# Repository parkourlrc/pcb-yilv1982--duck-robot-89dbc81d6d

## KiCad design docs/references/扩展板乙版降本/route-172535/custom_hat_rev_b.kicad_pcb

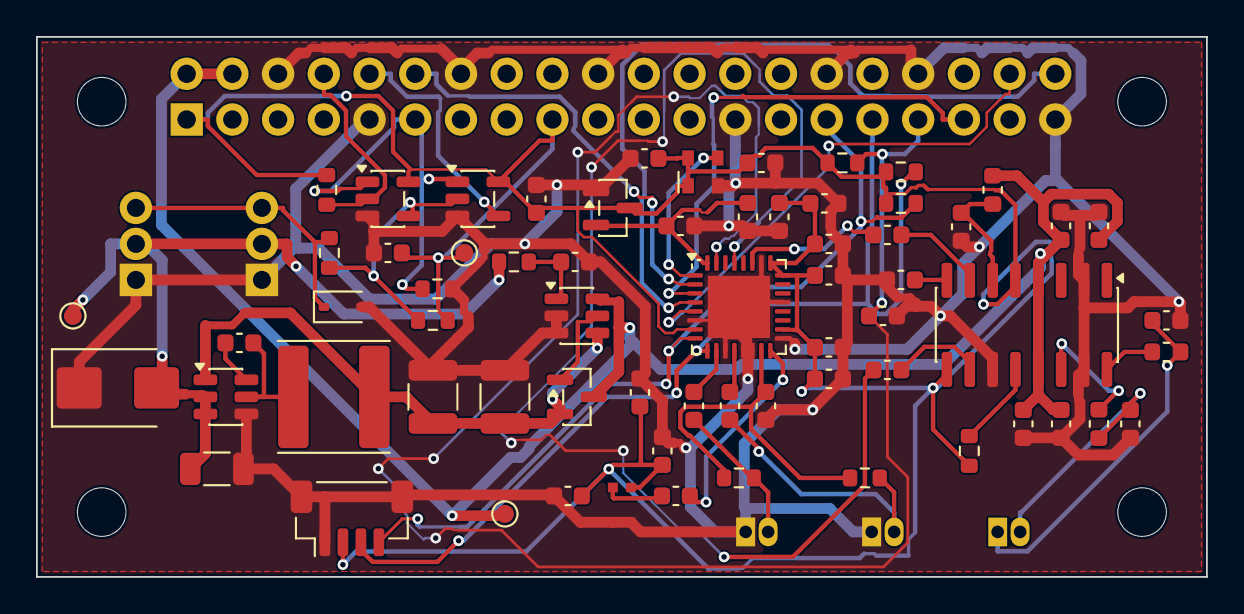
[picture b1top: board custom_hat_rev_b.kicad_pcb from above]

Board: 2 copper layers, 65.0 x 30.0 mm, 76 parts (1 on the bottom side), 41 nets.

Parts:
C301: 10uF35V; C_1206_3216Metric
C302, C305, C401, C402, C701, C704, C705, C707, C709, C711, C713, C721, C725, C735, C737: 100nF; C_0603_1608Metric
C303, C304: 22uF25V; C_1210_3225Metric
C702, C706, C708, C710, C712, C722, C723, C724, C731, C732, C733, C738: 1uF; C_0603_1608Metric
C703, C734, C736: 10uF; C_0603_1608Metric
C739, C740: 220pF; C_0603_1608Metric
D301: SMBJ12A; D_SMB
D401: 5.1V; D_SOD-323
FB701: 600R@100MHz; L_0603_1608Metric
FB702, FB703: 120R@100MHz; L_0603_1608Metric
H1, H2: MountingHole_2.7mm_M2.5; MountingHole_2.7_M2.5_Head4.5
H3, H4: MountingHole_2.7mm_M2.5
J101: RADXA_ZERO_3W; Radxa40P_Zhouri_B
J401, J402: SERVO_AMP2; AMP2007_3P_B
J502: QWIIC_3V3; JST_SH_BM04B-SRSS-TB_1x04-1MP_P1.00mm_Vertical
J505: J505_MIC; A1251_2P_B
J506: SPEAKER; A1251_2P_B
J507: J507_MIC; A1251_2P_B
L301: 6.8uH; L_Sunlord_SWPA6045S
MK701: MEMS_MIC; LMA2718_B
Q301: AO3404A; SOT-23
R301: 100R; R_0603_1608Metric
R401, R731: 100k; R_0603_1608Metric
R402, R403, R501, R502, R701: 10k; R_0603_1608Metric
R404: 0R; R_0603_1608Metric
R721, R722: 2.2k; R_0603_1608Metric
TP801: VBATT_2S_IN; TestPoint_Pad_D1.0mm
TP802: +5V; TestPoint_Pad_D1.0mm
TP803: +3V3; TestPoint_Pad_D1.0mm
U301: AP63205WU-7; TSOT-23-6
U302: LM5050-1; TSOT-23-6
U701: TLV320AIC3104; TI_RHB0032E_AIC3104_EP345
U702: XC6206P182MR; UMW_XC6206_SOT23_B
U801: SN74LVC1G126DBVR; SOT-23-5
U802: SN74LVC1G125DBVR; SOT-23-5
U803: PAM8406DR; SOIC-16_3.9x9.9mm_P1.27mm
Y701: 12MHz; Oscillator_SMD_Abracon_ASDMB-4Pin_2.5x2.0mm

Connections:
+1V8_CODEC: C703.1, C704.1, U701.32, U702.3
+3V3: C401.1, C402.1, C702.1, C705.1, C706.1, C707.1, C708.1, C709.1, C710.1, C711.1, C712.1, C713.1, C721.1, J101.1, J101.17, J502.2, MK701.4, R402.2, R403.2, R501.1, R502.1, R701.1, R731.1, TP803.1, U701.7, U701.18, U701.24, U701.25, U702.2, U801.5, U802.5, U803.5, U803.9, Y701.1, Y701.4
+5V: C734.1, C735.1, C736.1, C737.1, FB701.1, J101.2, J101.4, Q301.3, TP802.1, U302.6, U803.4, U803.13
+5V_PRE_IDEAL: C303.1, C304.1, L301.2, Q301.2, U301.1, U302.4
AMP_LEFT_INPUT: C731.2, U803.7
AMP_RIGHT_INPUT: C732.2, U803.10
AMP_R_N_RAW: FB702.1, U803.14
AMP_R_P_RAW: FB703.1, U803.16
AMP_VDD_FILT: C738.1, FB701.2, U803.6
AMP_VREF: C733.1, U803.8
AUDIO_AMP_EN: R731.2, U803.12
AUDIO_MCLK: U701.1, Y701.3
BUCK_BST: C302.1, U301.6
BUCK_SW: C302.2, L301.1, U301.5
CODEC_LEFT_LOP: C731.1, U701.27
CODEC_RIGHT_LOP: C732.1, U701.29
CODEC_RST: C701.1, J101.33, R701.2, U701.31
DXL_DATA: D401.1, J401.3, J402.3, R404.2
DXL_DATA_INT: R403.1, R404.1, U801.4, U802.2
DXL_DIR: J101.11, R401.1, U801.1, U802.1
I2C5_SCL: J101.29, J502.4, R502.2, U701.8
I2C5_SDA: J101.31, J502.3, R501.2, U701.9
I2S_BCLK: J101.12, U701.2
I2S_LRCK: J101.35, U701.3
I2S_SDI: J101.38, U701.5
I2S_SDO: J101.40, U701.4
IDEAL_GATE: Q301.1, U302.5
IDEAL_VS: C305.1, R301.2, U302.1
MICBIAS: C725.1, R721.1, R722.1, U701.15
MIC_EXT_L: C723.1, J505.2, R721.2
MIC_EXT_L_AC: C723.2, U701.10
MIC_EXT_R: C724.1, J507.2, R722.2
MIC_EXT_R_AC: C724.2, U701.12
MIC_ONBOARD_AC: C722.2, U701.16
MIC_ONBOARD_OUT: C722.1, MK701.1
POWER_GND: C301.2, C303.2, C304.2, C305.2, C401.2, C402.2, C701.2, C702.2, C703.2, C704.2, C705.2, C706.2, C707.2, C708.2, C709.2, C710.2, C711.2, C712.2, C713.2, C721.2, C725.2, C733.2, C734.2, C735.2, C736.2, C737.2, C738.2, C739.2, C740.2, D301.1, D401.2, J101.6, J101.9, J101.14, J101.20, J101.25, J101.30, J101.34, J101.39, J401.1, J402.1, J502.1, J502.MP, J505.1, J507.1, MK701.2, MK701.3, R401.2, U301.4, U302.2, U302.3, U701.6, U701.11, U701.13, U701.14, U701.17, U701.21, U701.26, U701.33, U702.1, U801.3, U802.3, U803.2, U803.11, U803.15, Y701.2
SPK_N: C739.1, FB702.2, J506.2
SPK_P: C740.1, FB703.2, J506.1
UART2_RX: J101.10, U802.4
UART2_TX: J101.8, R402.1, U801.2
VBATT_2S_IN: C301.1, D301.2, J401.2, J402.2, R301.1, TP801.1, U301.2, U301.3
